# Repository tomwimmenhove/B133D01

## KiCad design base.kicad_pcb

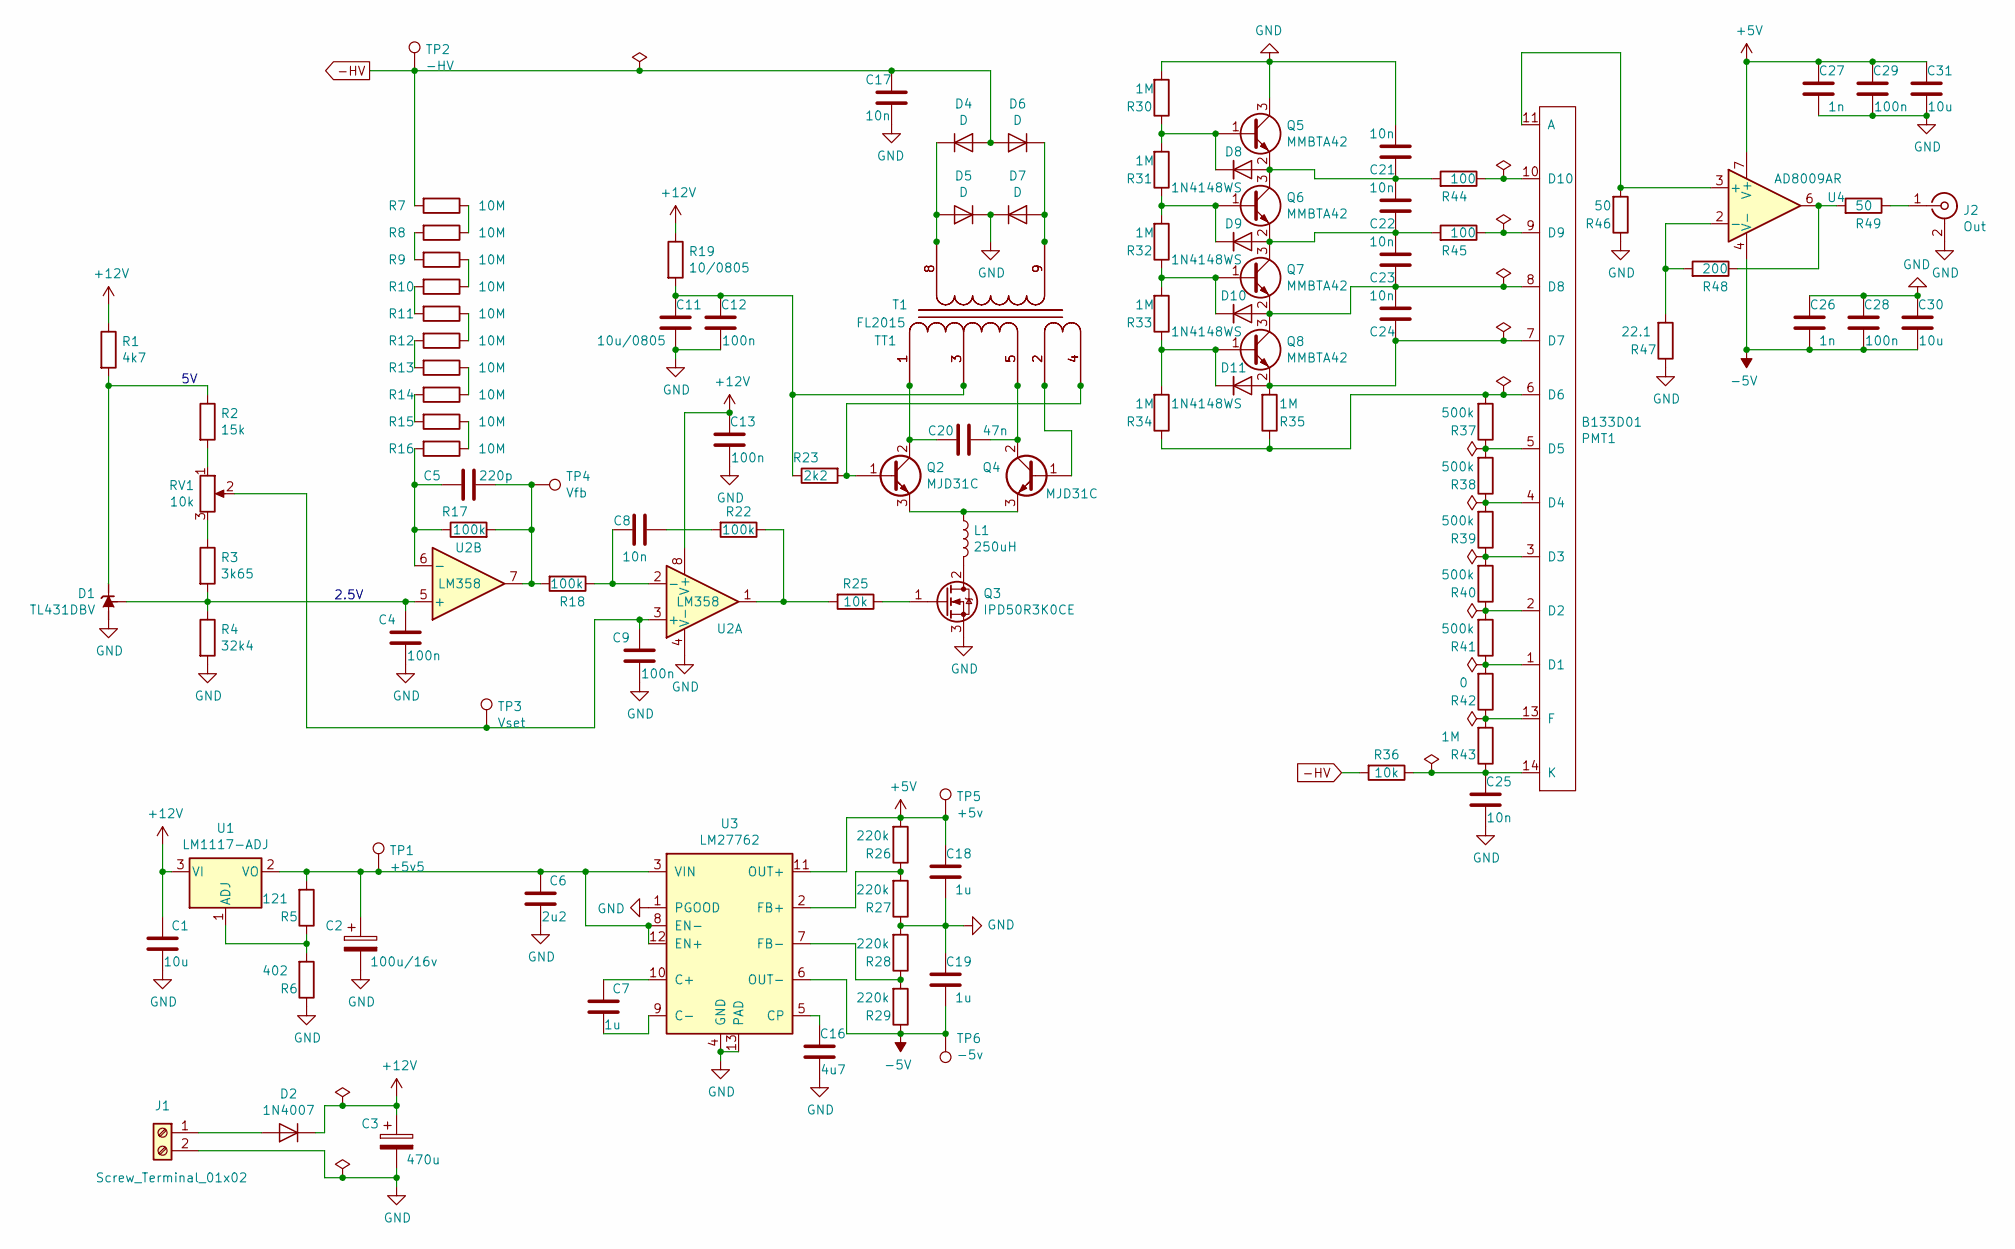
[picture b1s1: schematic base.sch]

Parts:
C1: 10u; C_0805_2012Metric
C2: 100u/16v; CP_EIA-7343-30_AVX-N
C3: 470u; CP_EIA-7360-38_Kemet-E
C4, C9, C12, C13, C28, C29: 100n; C_0603_1608Metric
C5: 220p; C_0603_1608Metric
C6: 2u2; C_0603_1608Metric
C7, C18, C19: 1u; C_0603_1608Metric
C8: 10n; C_0603_1608Metric
C11: 10u/0805; C_0805_2012Metric
C16: 4u7; C_0603_1608Metric
C17, C25: 10n; C_Disc_D10.5mm_W5.0mm_P7.50mm
C20: 47n; C_Rect_L7.2mm_W3.5mm_P5.00mm_FKS2_FKP2_MKS2_MKP2
C21, C22, C23, C24: 10n; C_0805_2012Metric
C26, C27: 1n; C_0603_1608Metric
C30, C31: 10u; C_0603_1608Metric
D1: TL431DBV; SOT-23-5
D2: 1N4007; D_SMB
D4, D5, D6, D7: D; D_A-405_P12.70mm_Horizontal
D8, D9, D10, D11: 1N4148WS; D_SOD-323
J1: Screw_Terminal_01x02; TerminalBlock_4Ucon_1x02_P3.50mm_Horizontal
J2: Out; SMA_Amphenol_132291-12_Vertical
L1: 250uH; L_Taiyo-Yuden_NR-80xx
PMT1: B133D01
Q2, Q4: MJD31C; TO-252-2
Q3: IPD50R3K0CE; TO-252-2
Q5, Q6, Q7, Q8: MMBTA42; SOT-23
R1: 4k7; R_0603_1608Metric
R2: 15k; R_0603_1608Metric
R3: 3k65; R_0603_1608Metric
R4: 32k4; R_0603_1608Metric
R5: 121; R_0603_1608Metric
R6: 402; R_0603_1608Metric
R7, R8, R9, R10, R11, R12, R13, R14, R15, R16: 10M; R_0805_2012Metric
R17, R18, R22: 100k; R_0603_1608Metric
R19: 10/0805; R_0805_2012Metric
R23: 2k2; R_0805_2012Metric
R25: 10k; R_0603_1608Metric
R26, R27, R28, R29: 220k; R_0603_1608Metric
R30, R31, R32, R33, R34, R35: 1M; R_0805_2012Metric
R36: 10k; R_0805_2012Metric
R37, R38, R39, R40, R41: 500k; R_0805_2012Metric
R42: 0; R_0603_1608Metric
R43: 1M; R_1206_3216Metric
R44, R45: 100; R_0603_1608Metric
R46: 50; R_0603_1608Metric
R47: 22.1; R_0603_1608Metric
R48: 200; R_0603_1608Metric
R49: 50; R_0805_2012Metric
RV1: 10k; Potentiometer_Bourns_3314J_Vertical
T1: FL2015; FL2015-4LB
TP1: +5v5; TestPoint_Pad_D1.5mm
TP2: -HV; TestPoint_Pad_D1.5mm
TP3: Vset; TestPoint_Pad_D1.5mm
TP4: Vfb; TestPoint_Pad_D1.5mm
TP5: +5v; TestPoint_Pad_D1.5mm
TP6: -5v; TestPoint_Pad_D1.5mm
TT1: FL2015; G23736
U1: LM1117-ADJ; SOT-223-3_TabPin2
U2: LM358; SOIC-8_3.9x4.9mm_P1.27mm
U3: LM27762; WSON-12-1EP_3x2mm_P0.5mm_EP1x2.65_ThermalVias
U4: AD8009AR; SOIC-8_3.9x4.9mm_P1.27mm

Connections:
+5V: C18.1, C27.1, C29.1, C31.1, R26.2, TP5.1, U3.11 (OUT+), U4.7 (V+)
+12V: C1.1, C3.1, C13.1, D2.1 (K), R1.1, R19.1, U1.3 (VI), U2.8 (V+)
-5V: C19.2, C26.2, C28.2, C30.2, R29.1, TP6.1, U3.6 (OUT-), U4.4 (V-)
-HV: C17.1, D4.2 (A), D6.2 (A), R7.2, R36.2, TP2.1
GND: C1.2, C2.2, C3.2, C4.2, C6.2, C9.2, C11.2, C12.2, C13.2, C16.2, C17.2, C18.2, C19.1, C21.2, C25.2, C26.1, C27.2, C28.1, C29.2, C30.1, C31.2, D1.5 (A), D5.1 (K), D7.1 (K), J1.2, J2.2 (Ext), Q3.3 (S), Q5.3 (C), R4.2, R6.1, R27.1, R28.2, R30.2, R46.1, R47.1, U2.4 (V-), U3.1 (PGOOD), U3.4 (GND), U3.13 (PAD)
unnamed: C2.1, C6.1, R5.2, TP1.1, U1.2 (VO), U3.3 (VIN), U3.8 (EN-), U3.12 (EN+)
unnamed: C4.1, D1.4 (REF), R3.2, R4.1, U2.5 (+)
unnamed: C5.1, R16.2, R17.1, U2.6 (-)
unnamed: C5.2, R17.2, R18.2, TP4.1, U2.7
unnamed: C7.1, U3.10 (C+)
unnamed: C7.2, U3.9 (C-)
unnamed: C8.1, R22.2
unnamed: C8.2, R18.1, U2.2 (-)
unnamed: C9.1, RV1.2, TP3.1, U2.3 (+)
unnamed: C11.1, C12.1, R19.2, R23.1, T1.3, TT1.3
unnamed: C16.1, U3.5 (CP)
unnamed: C20.1, Q2.2 (C), T1.1, TT1.1
unnamed: C20.2, Q4.2 (C), T1.5, TT1.5
unnamed: C21.1, C22.2, D8.2 (A), Q5.2 (E), Q6.3 (C), R44.2
unnamed: C22.1, C23.2, D9.2 (A), Q6.2 (E), Q7.3 (C), R45.2
unnamed: C23.1, C24.2, D10.2 (A), PMT1.8 (D8), Q7.2 (E), Q8.3 (C)
unnamed: C24.1, D11.2 (A), PMT1.7 (D7), Q8.2 (E), R35.2
unnamed: C25.1, PMT1.14 (K), R36.1, R43.1
unnamed: D1.3 (K), R1.2, R2.1
unnamed: D2.2 (A), J1.1
unnamed: D4.1 (K), D5.2 (A), T1.8, TT1.8
unnamed: D6.1 (K), D7.2 (A), T1.9, TT1.9
unnamed: D8.1 (K), Q5.1 (B), R30.1, R31.2
unnamed: D9.1 (K), Q6.1 (B), R31.1, R32.2
unnamed: D10.1 (K), Q7.1 (B), R32.1, R33.2
unnamed: D11.1 (K), Q8.1 (B), R33.1, R34.2
unnamed: J2.1 (In), R49.1
unnamed 32: L1.1, Q2.3 (E), Q4.3 (E); also elsewhere on the board
unnamed 33: L1.2, Q3.2 (D); also elsewhere on the board
unnamed: PMT1.1 (D1), R41.1, R42.2
unnamed: PMT1.2 (D2), R40.1, R41.2
unnamed: PMT1.3 (D3), R39.1, R40.2
unnamed: PMT1.4 (D4), R38.1, R39.2
unnamed: PMT1.5 (D5), R37.1, R38.2
unnamed: PMT1.6 (D6), R34.1, R35.1, R37.2
unnamed: PMT1.9 (D9), R45.1
unnamed: PMT1.10 (D10), R44.1
unnamed: PMT1.11 (A), R46.2, U4.3 (+)
unnamed: PMT1.13 (F), R42.1, R43.2
unnamed: Q2.1 (B), R23.2, T1.4, TT1.4
unnamed: Q3.1 (G), R25.1
unnamed: Q4.1 (B), T1.2, TT1.2
unnamed: R2.2, RV1.1
unnamed: R3.1, RV1.3
unnamed: R5.1, R6.2, U1.1 (ADJ)
unnamed: R7.1, R8.1
unnamed: R8.2, R9.2
unnamed: R9.1, R10.1
unnamed: R10.2, R11.2
unnamed: R11.1, R12.1
unnamed: R12.2, R13.2
unnamed: R13.1, R14.1
unnamed: R14.2, R15.2
unnamed: R15.1, R16.1
unnamed: R22.1, R25.2, U2.1
unnamed: R26.1, R27.2, U3.2 (FB+)
unnamed: R28.1, R29.2, U3.7 (FB-)
unnamed: R47.2, R48.2, U4.2 (-)
unnamed: R48.1, R49.2, U4.6

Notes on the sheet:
2.5V

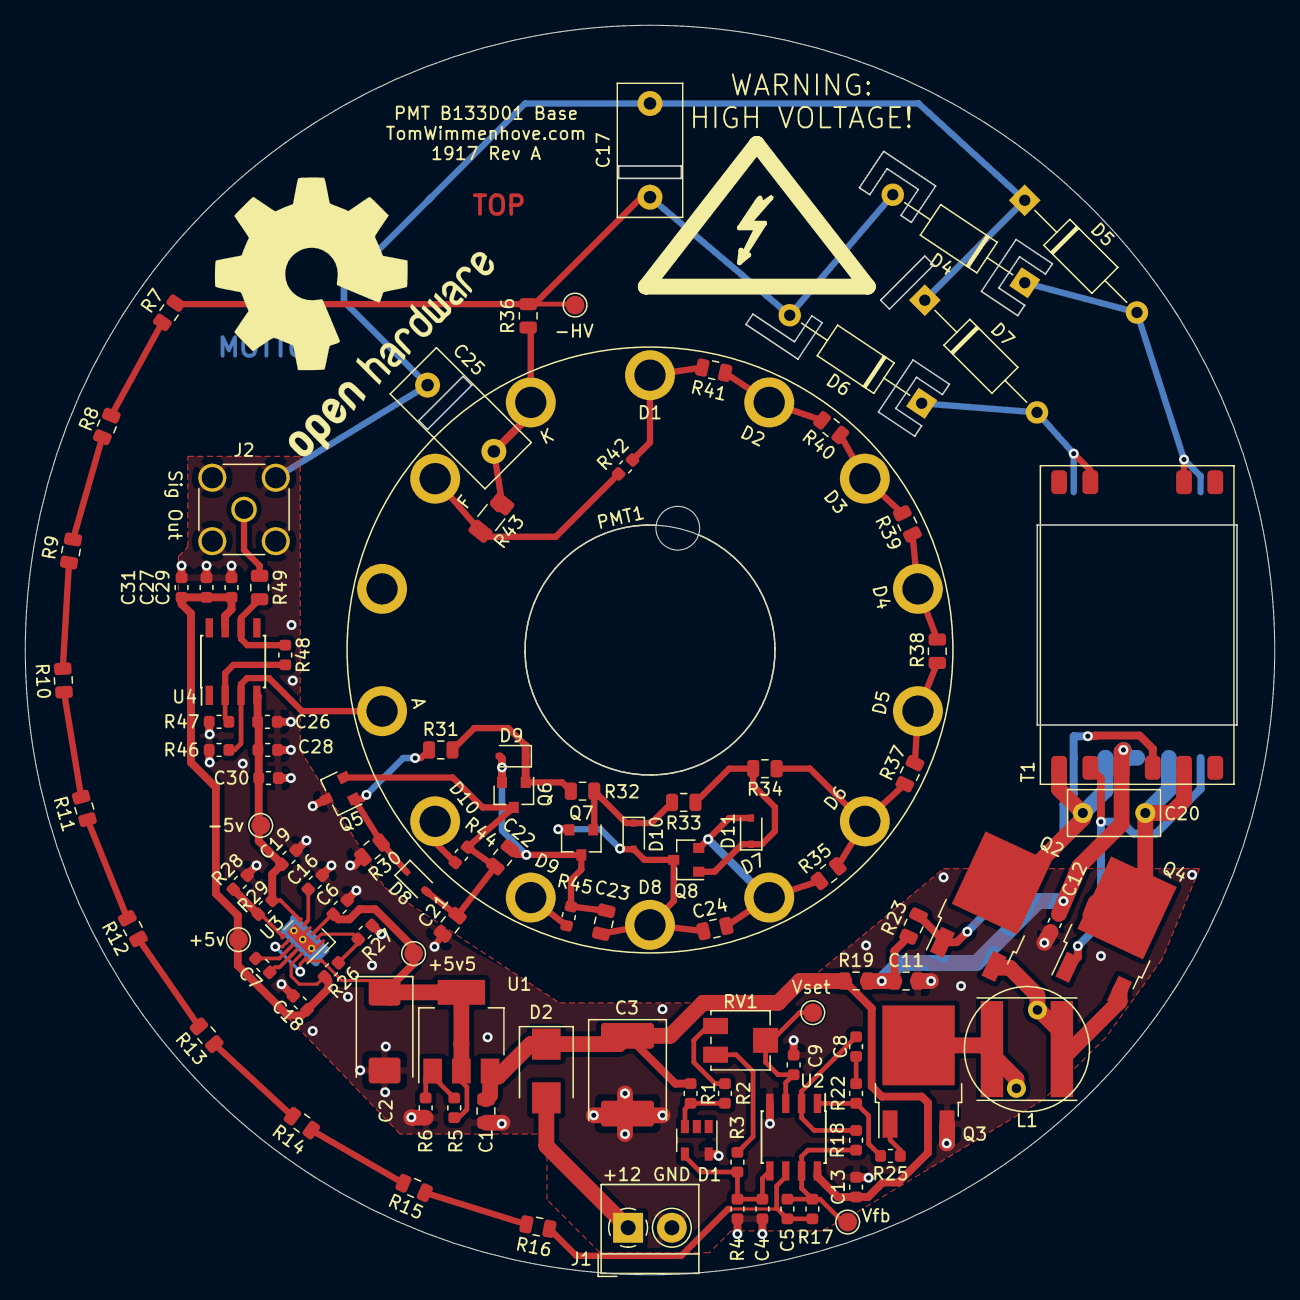
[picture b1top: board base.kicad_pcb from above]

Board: 2 copper layers, 99.9 x 99.9 mm, 117 parts (0 on the bottom side), 64 nets.

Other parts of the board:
HV1: Symbol_Highvoltage_Type2_SilkScreenTop_Small
L**: L
Slot**: ISlot
Slot**#2, Slot**#6: ISlot
Slot**#3, Slot**#4, Slot**#7: CSlot
Slot**#5: LSlot

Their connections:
unnamed 32: L**.1; also elsewhere on the board
unnamed 33: L**.2; also elsewhere on the board

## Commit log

2019-04-23 Backup
2019-04-24 Added optional G23736 (electronic goldmine) footprint
2019-04-27 More routing. Removed excessive ripper remover
2019-04-27 Accidentally used PNP bjt's for royer drivers
2019-04-27 Moved stuff around. Added isolation slots.
2019-04-27 Fixed PMT hole size
2019-04-28 Added testpoints
2019-04-28 Added transformer 3d model
2019-04-28 Forgot to add file
2019-04-28 Library name juggling
2019-04-28 Removed unused libraries
2019-04-28 Fixed undriven pins errors in DRC
2019-04-28 moved files around. Changed cutout for alternative transformer package
2019-04-28 Fixed DRC
2019-04-28 Minor fixes
2019-05-04 Changed royer circuit cap to TH
2019-05-04 Fixed some footprints and values
2019-05-04 Added slots foot prints
2019-05-04 Small fix
2019-05-05 Layout changes
2019-05-05 Added alternative L
